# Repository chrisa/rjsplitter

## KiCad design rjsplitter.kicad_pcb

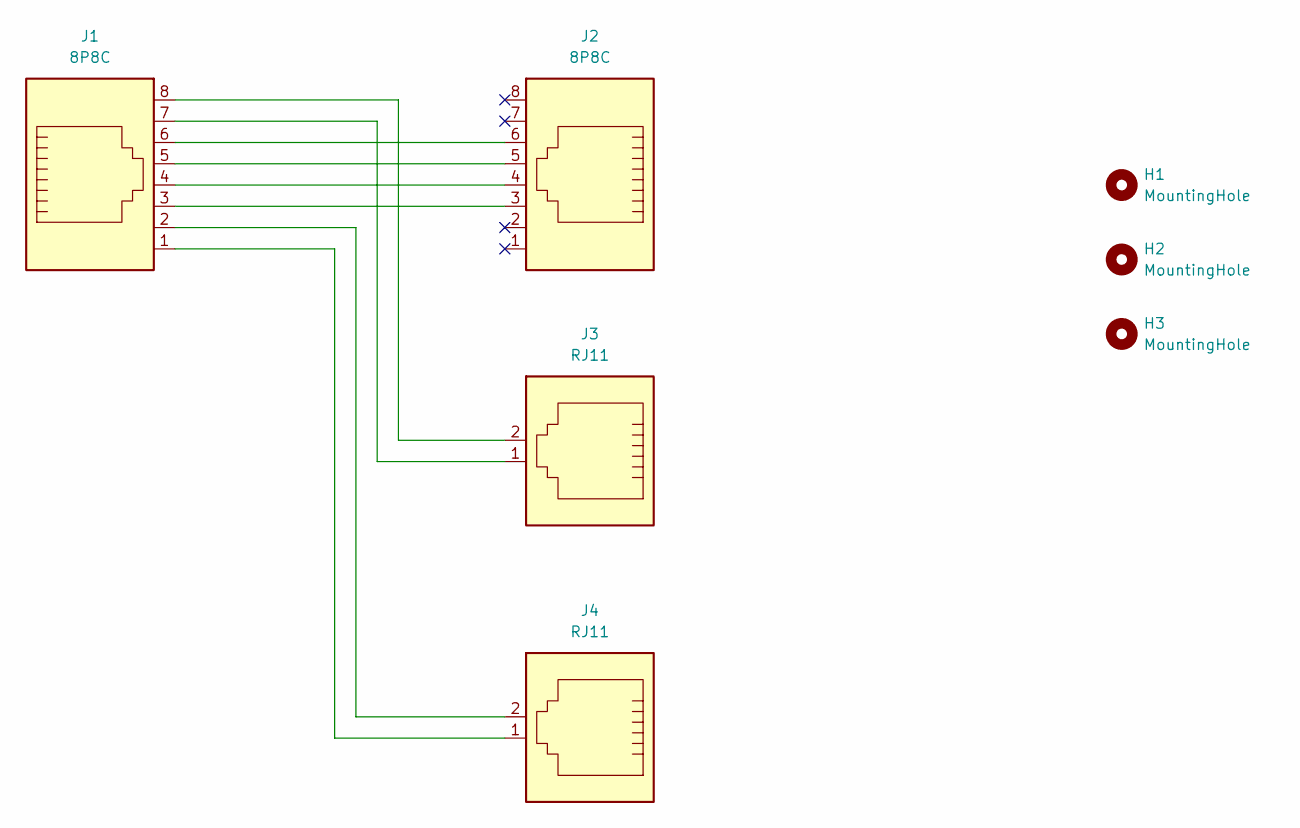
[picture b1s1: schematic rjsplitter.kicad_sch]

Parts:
H1, H2, H3: MountingHole; MountingHole_3.2mm_M3
J1, J2: 8P8C; RJ45_Amphenol_54602-x08_Horizontal
J3, J4: RJ11; AMPHENOL_54601-906WPLF

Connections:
unnamed: J1.1, J4.1
unnamed: J1.2, J4.2
unnamed: J1.3, J2.3
unnamed: J1.4, J2.4
unnamed: J1.5, J2.5
unnamed: J1.6, J2.6
unnamed: J1.7, J3.1
unnamed: J1.8, J3.2

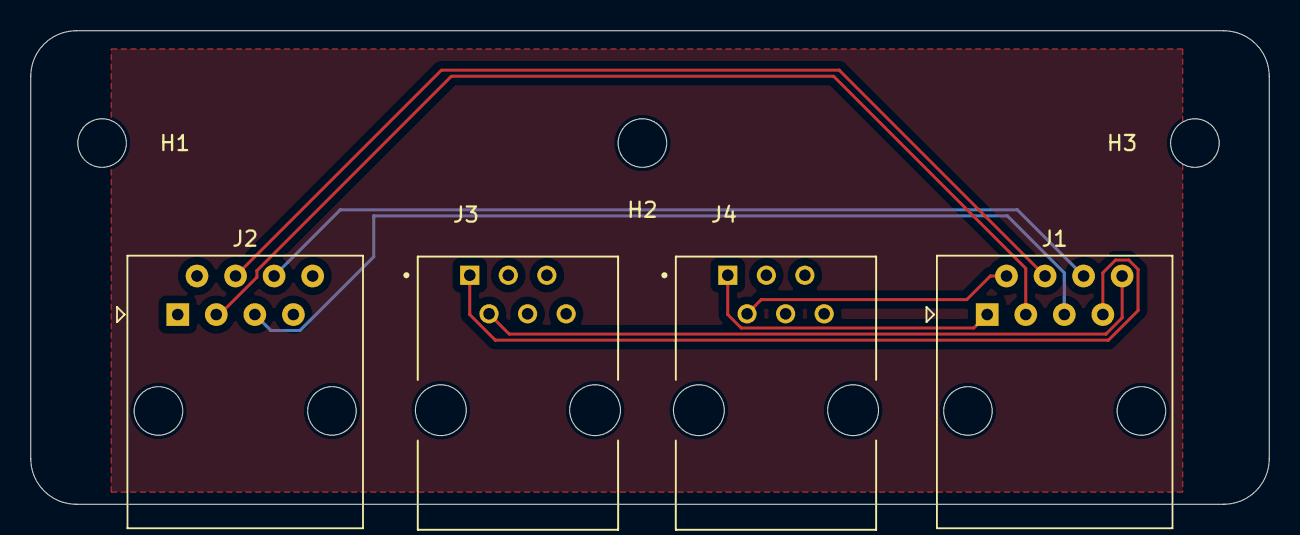
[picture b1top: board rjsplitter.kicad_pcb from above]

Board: 2 copper layers, 81.6 x 31.2 mm, 7 parts (0 on the bottom side), 8 nets.

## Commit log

2025-04-26 Initial RJ45 splitter
2025-04-26 Add Kibot
2025-05-03 Switch to a mix of RJ45 and RJ11.
